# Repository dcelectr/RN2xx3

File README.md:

# RN2xx3

Board for Microchip RN2483 or RN2093

This board was designed based on the Microchip design recommendations found in the datasheet for the RF output traces and ground plane stitching.

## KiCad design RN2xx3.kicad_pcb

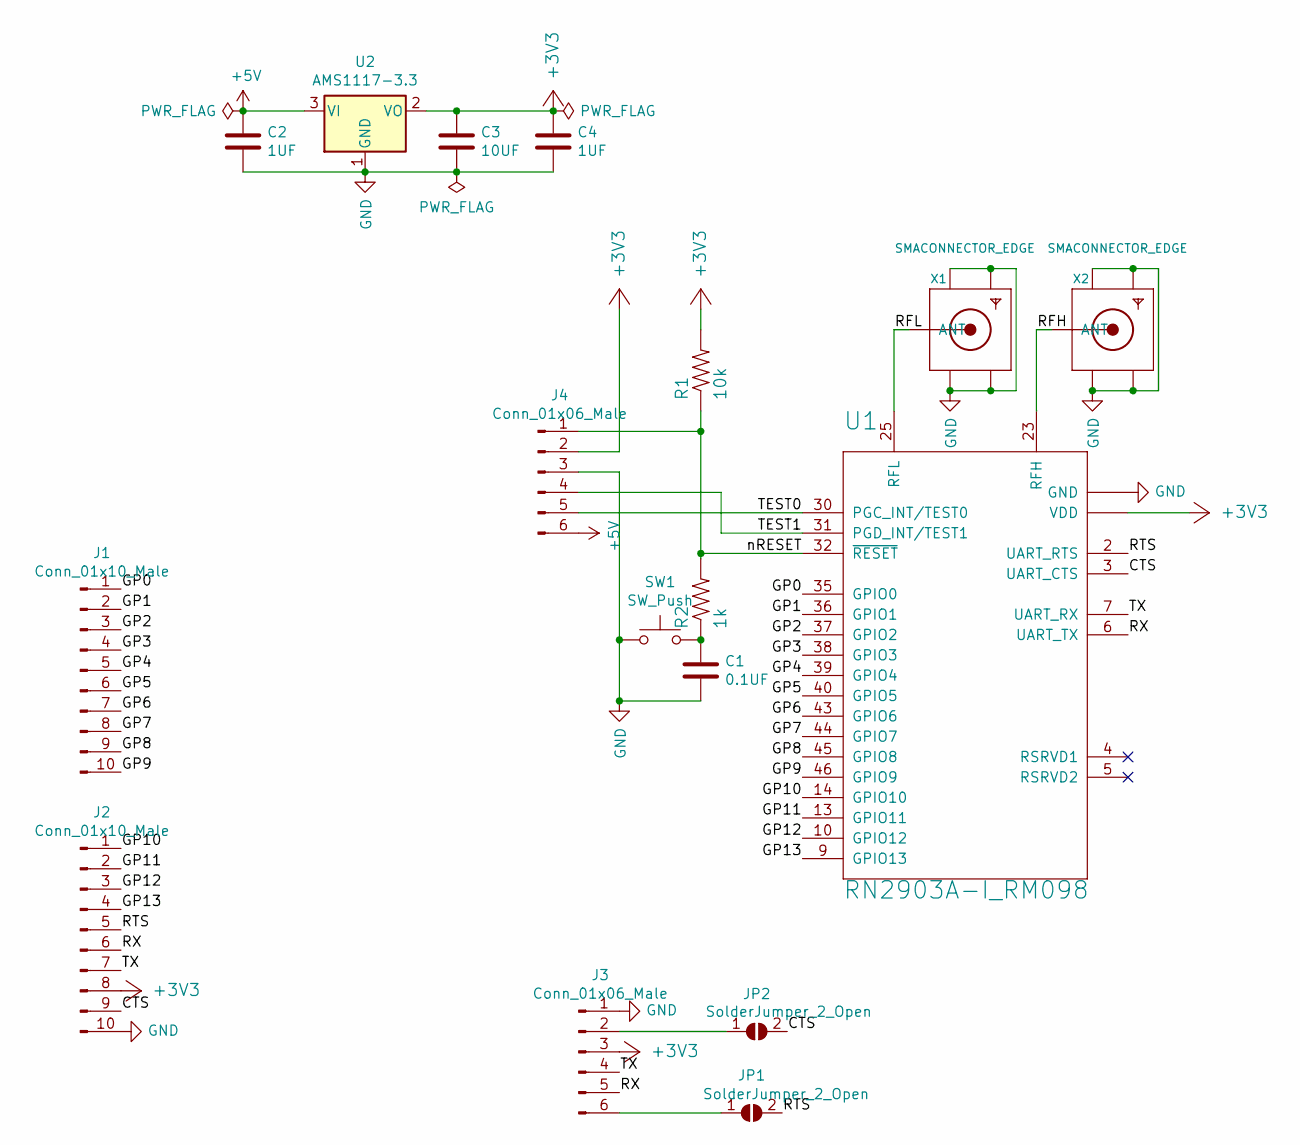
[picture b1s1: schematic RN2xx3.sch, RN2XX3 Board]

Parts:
C1: 0.1UF; C_0805_2012Metric_Pad1.15x1.40mm_HandSolder
C2, C4: 1UF; C_0805_2012Metric_Pad1.15x1.40mm_HandSolder
C3: 10UF; C_0805_2012Metric_Pad1.15x1.40mm_HandSolder
J1, J2: Conn_01x10_Male; PinHeader_1x10_P2.54mm_Vertical
J3, J4: Conn_01x06_Male; PinHeader_1x06_P2.54mm_Vertical
JP1, JP2: SolderJumper_2_Open; SolderJumper-2_P1.3mm_Open_RoundedPad1.0x1.5mm
R1: 10k; R_0603_1608Metric_Pad1.05x0.95mm_HandSolder
R2: 1k; R_0603_1608Metric_Pad1.05x0.95mm_HandSolder
SW1: SW_Push; SW_SPST_CK_KXT3_3D_Handsolder
U1: RN2903A-I_RM098; Microchip_RN2903A-w_3D
U2: AMS1117-3.3; SOT-223-3_TabPin2
X1, X2: SMACONNECTOR_EDGE; SMA_RF_Solutions

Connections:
+3V3: C3.1, C4.1, J2.8, J3.3, J4.2, R1.2, U1.12 (VDD), U1.34 (VDD), U2.2 (VO)
+5V: C2.1, J4.6, U2.3 (VI)
/CTS: J2.9, JP2.2 (B), U1.3 (UART_CTS)
/GP0: J1.1, U1.35 (GPIO0)
/GP1: J1.2, U1.36 (GPIO1)
/GP2: J1.3, U1.37 (GPIO2)
/GP3: J1.4, U1.38 (GPIO3)
/GP4: J1.5, U1.39 (GPIO4)
/GP5: J1.6, U1.40 (GPIO5)
/GP6: J1.7, U1.43 (GPIO6)
/GP7: J1.8, U1.44 (GPIO7)
/GP8: J1.9, U1.45 (GPIO8)
/GP9: J1.10, U1.46 (GPIO9)
/GP10: J2.1, U1.14 (GPIO10)
/GP11: J2.2, U1.13 (GPIO11)
/GP12: J2.3, U1.10 (GPIO12)
/GP13: J2.4, U1.9 (GPIO13)
/RFH: U1.23 (RFH), X2.P (ANT)
/RFL: U1.25 (RFL), X1.P (ANT)
/RTS: J2.5, JP1.2 (B), U1.2 (UART_RTS)
/RX: J2.6, J3.5, U1.6 (UART_TX)
/TEST0: J4.5, U1.30 (PGC_INT/TEST0)
/TEST1: J4.4, U1.31 (PGD_INT/TEST1)
/TX: J2.7, J3.4, U1.7 (UART_RX)
/nRESET: J4.1, R1.1, R2.2, U1.32 (~RESET)
GND: C1.2, C2.2, C3.2, C4.2, J2.10, J3.1, J4.3, SW1.1, U1.1 (GND), U1.8 (GND), U1.11 (GND), U1.20 (GND), U1.21 (GND), U1.22 (GND), U1.24 (GND), U1.26 (GND), U1.27 (GND), U1.28 (GND), U1.33 (GND), U1.41 (GND), U1.47 (GND), U2.1 (GND), X1.GND@1 (GND4), X1.GND@2 (GND3), X1.GND@3 (GND2), X1.GND@4 (GND1), X2.GND@1 (GND4), X2.GND@2 (GND3), X2.GND@3 (GND2), X2.GND@4 (GND1)
unnamed: C1.1, R2.1, SW1.2
unnamed: J3.6, JP1.1 (A)

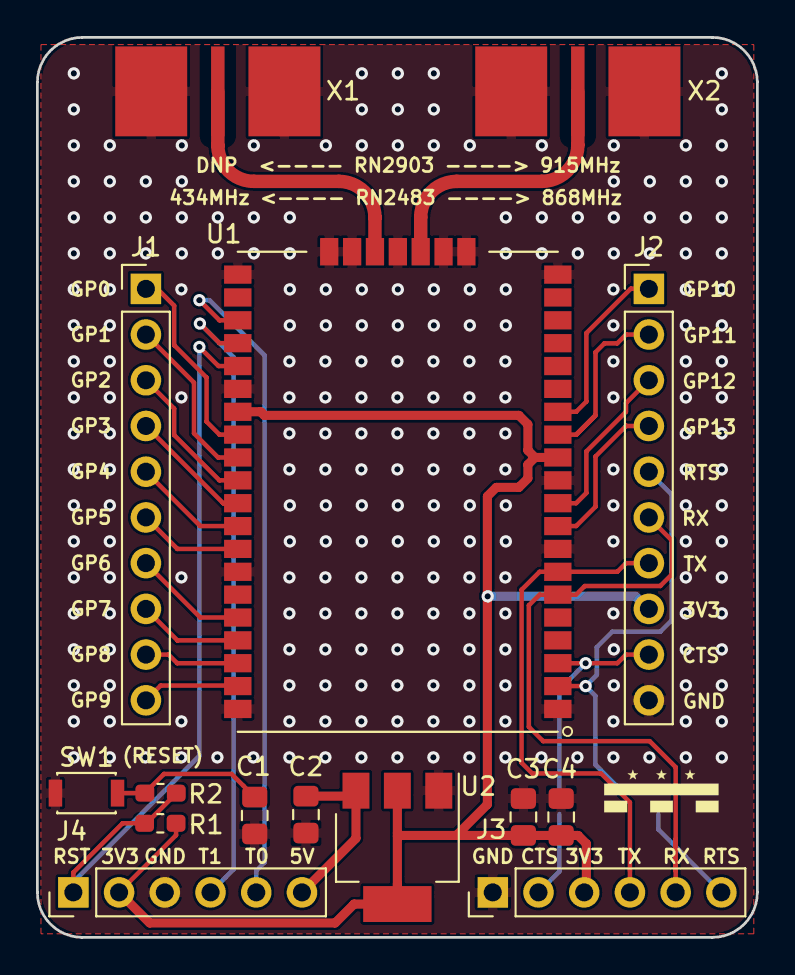
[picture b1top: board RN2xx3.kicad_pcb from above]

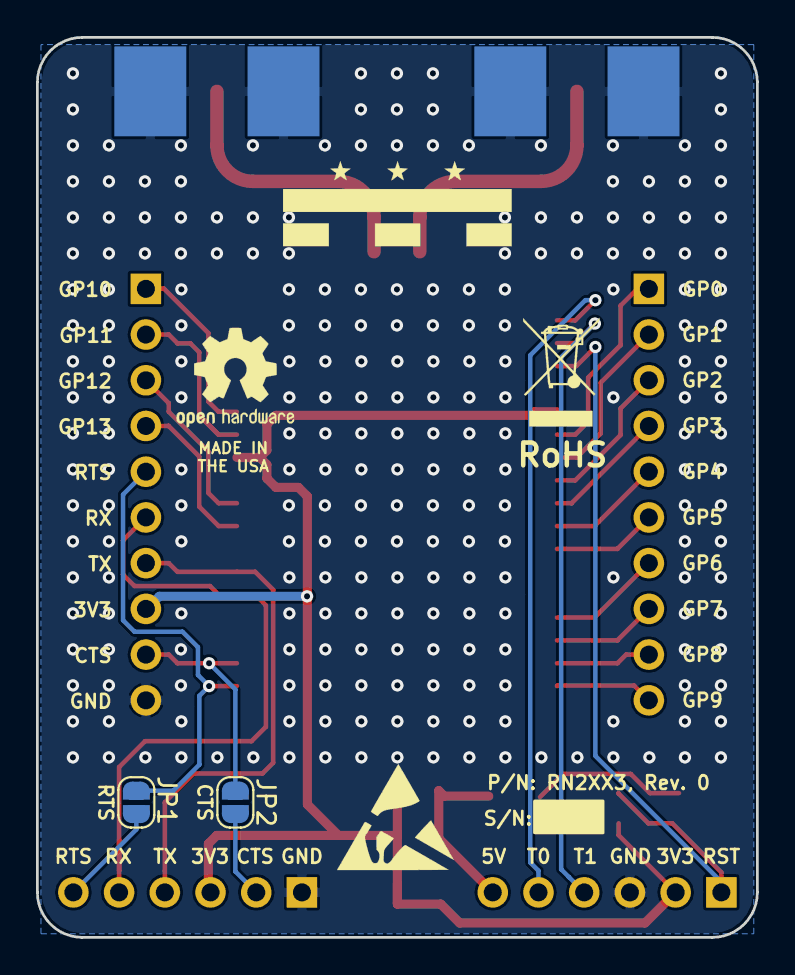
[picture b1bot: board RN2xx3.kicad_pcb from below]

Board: 2 copper layers, 40.0 x 50.0 mm, 17 parts (2 on the bottom side), 28 nets.
